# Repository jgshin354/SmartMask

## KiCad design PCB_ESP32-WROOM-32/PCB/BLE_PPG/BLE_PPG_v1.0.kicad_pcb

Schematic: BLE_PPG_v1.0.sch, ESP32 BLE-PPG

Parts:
J1: 532610471(angled); Molex_PicoBlade_53261-0471_1x04-1MP_P1.25mm_Horizontal
J2: 532610271(angled); Molex_PicoBlade_53261-0271_1x02-1MP_P1.25mm_Horizontal
R1: 10k; R_0603_1608Metric
U1: ESP32-WROOM-32; ESP32-WROOM-32-Min_keepout
U2: OSTSen-30101
U3, U4: PTS830GM140SMTRLFS; PTS830GM140SMTRLFS_mod

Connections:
/ESP32_EN: R1.1, U1.3 (EN), U4.1, U4.2
/ESP_IO0: U1.25 (IO0), U3.1, U3.2
/ESP_RX: J1.3, U1.34 (RXD0/IO3)
/ESP_TX: J1.2, U1.35 (TXD0/IO1)
/I2C_SCL: U1.36 (IO22), U2.3
/I2C_SDA: U1.33 (IO21), U2.4
GND: J1.4, J2.2, U1.1 (GND), U1.15 (GND), U1.38 (GND), U1.39 (GND), U2.2, U3.3, U3.4, U4.3, U4.4
VCC: J1.1, J2.1, R1.2, U1.2 (VDD), U2.1

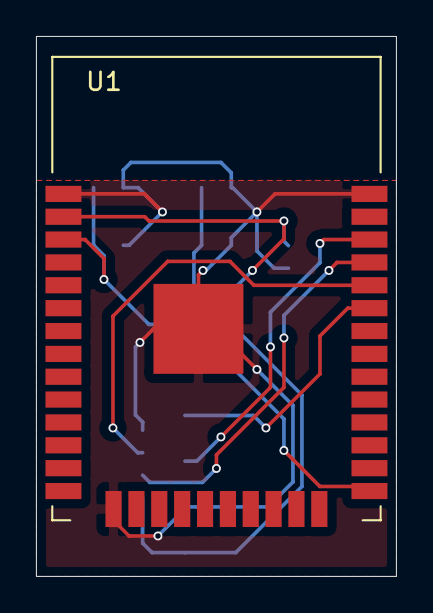
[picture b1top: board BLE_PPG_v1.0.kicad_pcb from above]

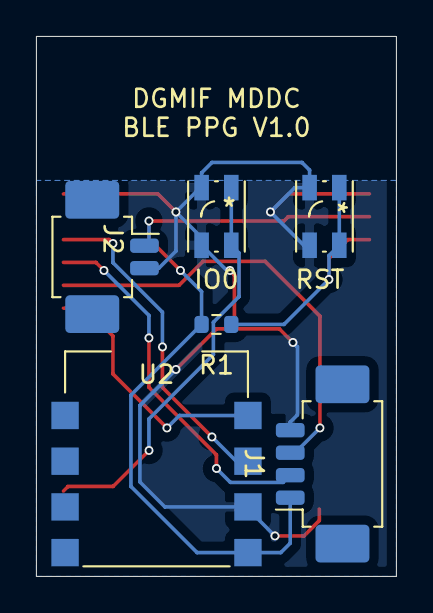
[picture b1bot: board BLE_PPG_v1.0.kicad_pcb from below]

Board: 2 copper layers, 20.0 x 30.0 mm, 7 parts (6 on the bottom side), 8 nets.

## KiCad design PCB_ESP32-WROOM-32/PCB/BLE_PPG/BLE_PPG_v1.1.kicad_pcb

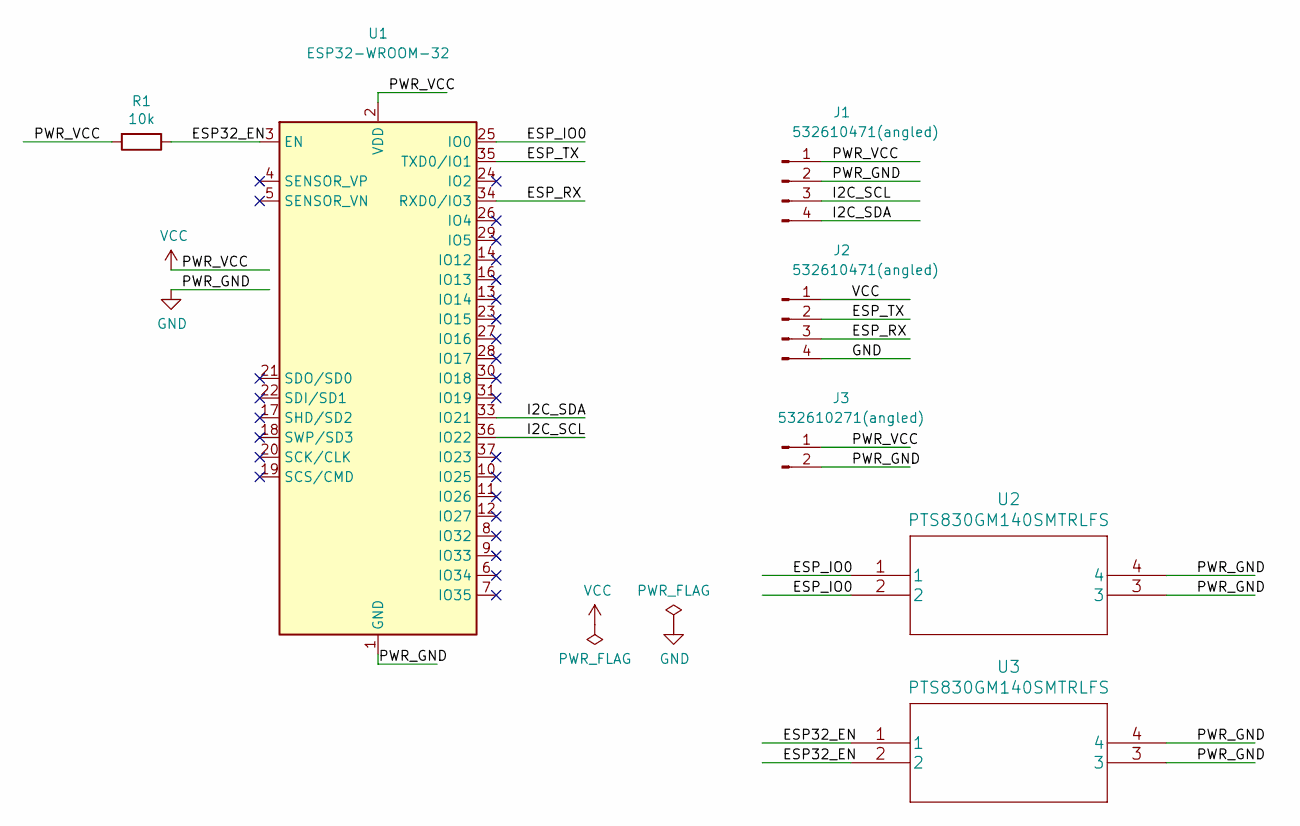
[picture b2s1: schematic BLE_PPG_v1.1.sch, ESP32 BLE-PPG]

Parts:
J1, J2: 532610471(angled); Molex_PicoBlade_53261-0471_1x04-1MP_P1.25mm_Horizontal
J3: 532610271(angled); Molex_PicoBlade_53261-0271_1x02-1MP_P1.25mm_Horizontal
R1: 10k; R_0603_1608Metric
U1: ESP32-WROOM-32; ESP32-WROOM-32-Min_keepout
U2, U3: PTS830GM140SMTRLFS; PTS830GM140SMTRLFS_mod

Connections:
/ESP32_EN: R1.1, U1.3 (EN), U3.1, U3.2
/ESP_IO0: U1.25 (IO0), U2.1, U2.2
/ESP_RX: J2.3, U1.34 (RXD0/IO3)
/ESP_TX: J2.2, U1.35 (TXD0/IO1)
/I2C_SCL: J1.3, U1.36 (IO22)
/I2C_SDA: J1.4, U1.33 (IO21)
GND: J1.2, J2.4, J3.2, U1.1 (GND), U1.15 (GND), U1.38 (GND), U1.39 (GND), U2.3, U2.4, U3.3, U3.4
VCC: J1.1, J2.1, J3.1, R1.2, U1.2 (VDD)

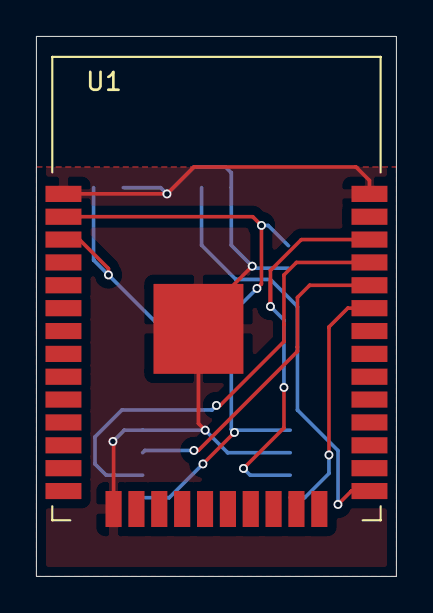
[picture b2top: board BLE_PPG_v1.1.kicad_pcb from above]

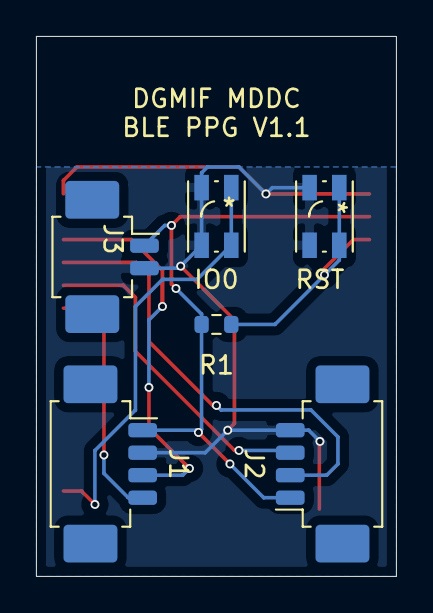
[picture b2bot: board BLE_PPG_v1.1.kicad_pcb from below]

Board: 2 copper layers, 20.0 x 30.0 mm, 7 parts (6 on the bottom side), 8 nets.

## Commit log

2021-06-23 PPG-Release(GUI & Firmware)
    PPG-Release(GUI & Firmware)
2021-07-05 ESP32_dev
2021-07-13 Adding Temperature Acquition
2021-07-14 ## 20210714-RGBLED-freq_mod-adv_freq 1.
    1. **Photobiomodulation only, no EEG Acquisition**
2021-07-27 Starrt Appinventor
